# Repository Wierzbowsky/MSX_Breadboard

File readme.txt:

Breadboard for MSX computers. Created by Wierzbowsky [RBSC]

Commercial usage is not allowed!

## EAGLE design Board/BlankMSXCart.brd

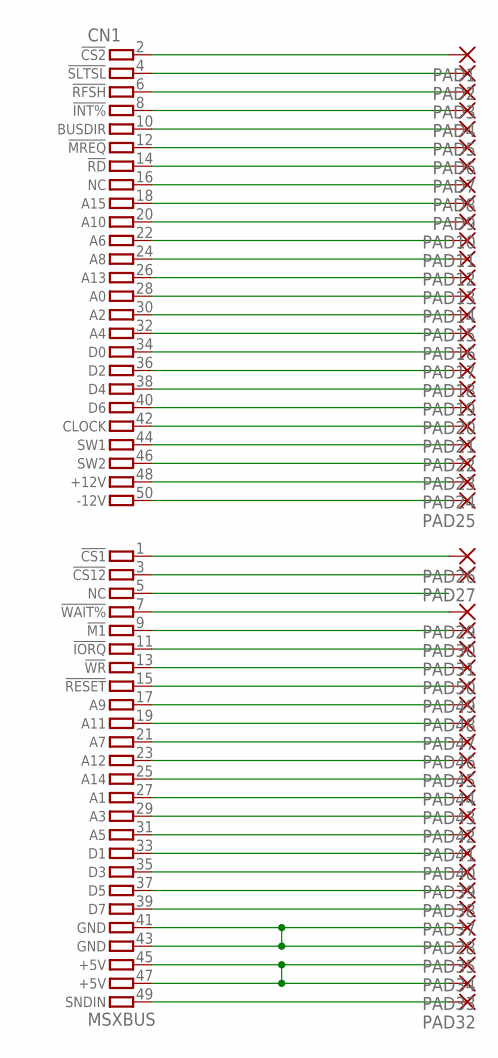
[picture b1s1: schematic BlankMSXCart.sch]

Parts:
CN1: MSXBUS; MSXBUS_EDGECONN
PAD1, PAD2, PAD3, PAD4, PAD5, PAD6, PAD7, PAD8, PAD9, PAD10, PAD11, PAD12, PAD13, PAD14, PAD15, PAD16, PAD17, PAD18, PAD19, PAD20, PAD21, PAD22, PAD23, PAD24, PAD25, PAD26, PAD27, PAD28, PAD29, PAD30, PAD31, PAD32, PAD33, PAD34, PAD35, PAD37, PAD38, PAD39, PAD40, PAD41, PAD42, PAD43, PAD44, PAD45, PAD46, PAD47, PAD48, PAD49, PAD50: 1,6/0,8

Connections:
+5V: CN1.45 (45.+5V), CN1.47 (47.+5V), PAD33.1, PAD34.1
GND: CN1.41 (41.GND), CN1.43 (43.GND), PAD28.1, PAD35.1
unnamed: CN1.2 (2.!CS2), PAD1.1
unnamed: CN1.4 (4.!SLTSL), PAD2.1
unnamed: CN1.6 (6.!RFSH), PAD3.1
unnamed: CN1.8 (8.!INT%), PAD4.1
unnamed: CN1.10 (10.BUSDIR), PAD5.1
unnamed: CN1.12 (12.!MREQ), PAD6.1
unnamed: CN1.14 (14.!RD), PAD7.1
unnamed: CN1.16 (16.NC), PAD8.1
unnamed: CN1.18 (18.A15), PAD9.1
unnamed: CN1.20 (20.A10), PAD10.1
unnamed: CN1.22 (22.A6), PAD11.1
unnamed: CN1.24 (24.A8), PAD12.1
unnamed: CN1.26 (26.A13), PAD13.1
unnamed: CN1.28 (28.A0), PAD14.1
unnamed: CN1.30 (30.A2), PAD15.1
unnamed: CN1.32 (32.A4), PAD16.1
unnamed: CN1.34 (34.D0), PAD17.1
unnamed: CN1.36 (36.D2), PAD18.1
unnamed: CN1.38 (38.D4), PAD19.1
unnamed: CN1.40 (40.D6), PAD20.1
unnamed: CN1.42 (42.CLOCK), PAD21.1
unnamed: CN1.44 (44.SW1), PAD22.1
unnamed: CN1.46 (46.SW2), PAD23.1
unnamed: CN1.48 (48.+12V), PAD24.1
unnamed: CN1.50 (50.-12V), PAD25.1
unnamed: CN1.1 (1.!CS1), PAD26.1
unnamed: CN1.3 (3.!CS12), PAD27.1
unnamed: CN1.7 (7.!WAIT%), PAD29.1
unnamed: CN1.9 (9.!M1), PAD30.1
unnamed: CN1.11 (11.!IORQ), PAD31.1
unnamed: CN1.49 (49.SNDIN), PAD32.1
unnamed: CN1.39 (39.D7), PAD37.1
unnamed: CN1.37 (37.D5), PAD38.1
unnamed: CN1.35 (35.D3), PAD39.1
unnamed: CN1.33 (33.D1), PAD40.1
unnamed: CN1.31 (31.A5), PAD41.1
unnamed: CN1.29 (29.A3), PAD42.1
unnamed: CN1.27 (27.A1), PAD43.1
unnamed: CN1.25 (25.A14), PAD44.1
unnamed: CN1.23 (23.A12), PAD45.1
unnamed: CN1.21 (21.A7), PAD46.1
unnamed: CN1.19 (19.A11), PAD47.1
unnamed: CN1.17 (17.A9), PAD48.1
unnamed: CN1.15 (15.!RESET), PAD49.1
unnamed: CN1.13 (13.!WR), PAD50.1

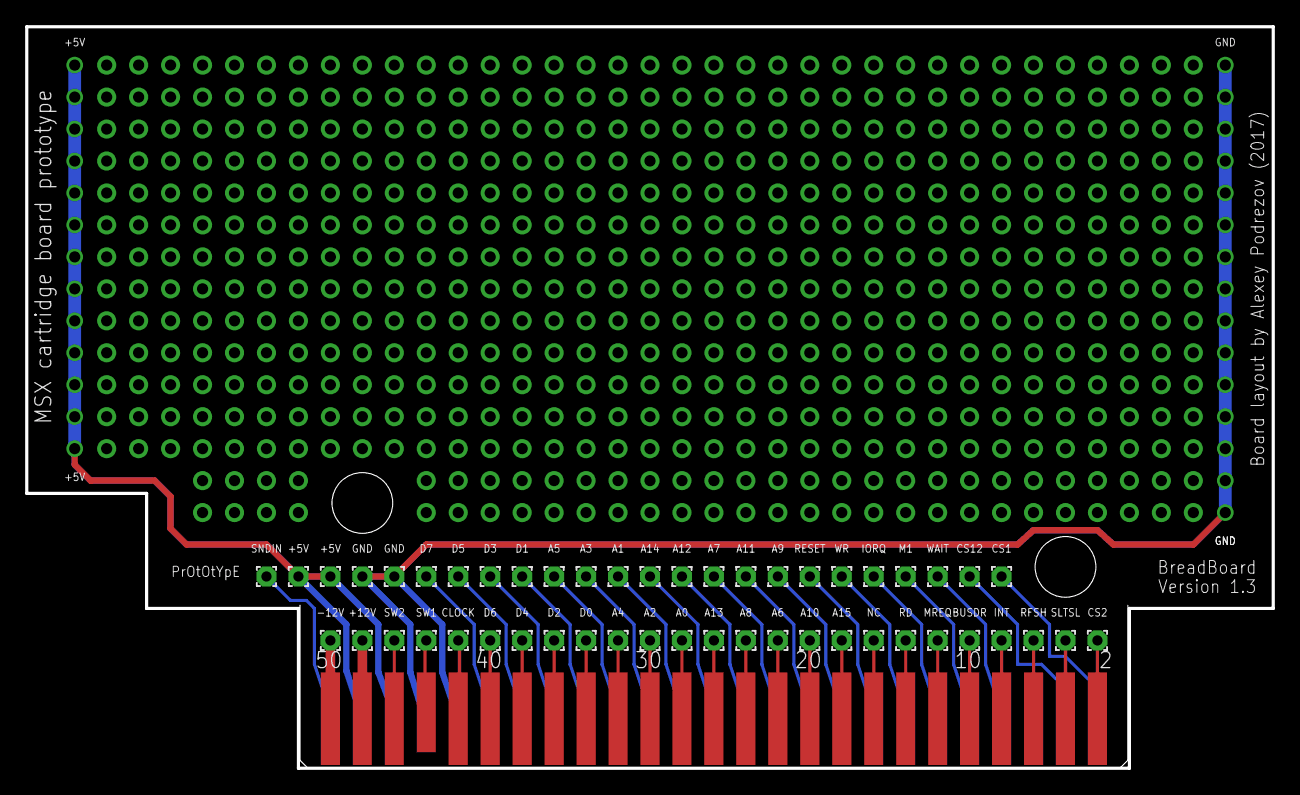
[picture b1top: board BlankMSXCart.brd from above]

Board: 2 copper layers, 99.1 x 58.9 mm, 50 parts (0 on the bottom side), 47 nets.

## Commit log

2017-05-03 :boom::camel: Added .gitattributes & .gitignore files
2017-05-03 Prototype board v1.2
2017-06-01 Made the board 1mm narrower for cheaper production
2020-10-10 Updated 10.10.2020
    Larger via holes + wider power and ground rails
2020-10-10 Updated 10.10.2020
    Readme added
